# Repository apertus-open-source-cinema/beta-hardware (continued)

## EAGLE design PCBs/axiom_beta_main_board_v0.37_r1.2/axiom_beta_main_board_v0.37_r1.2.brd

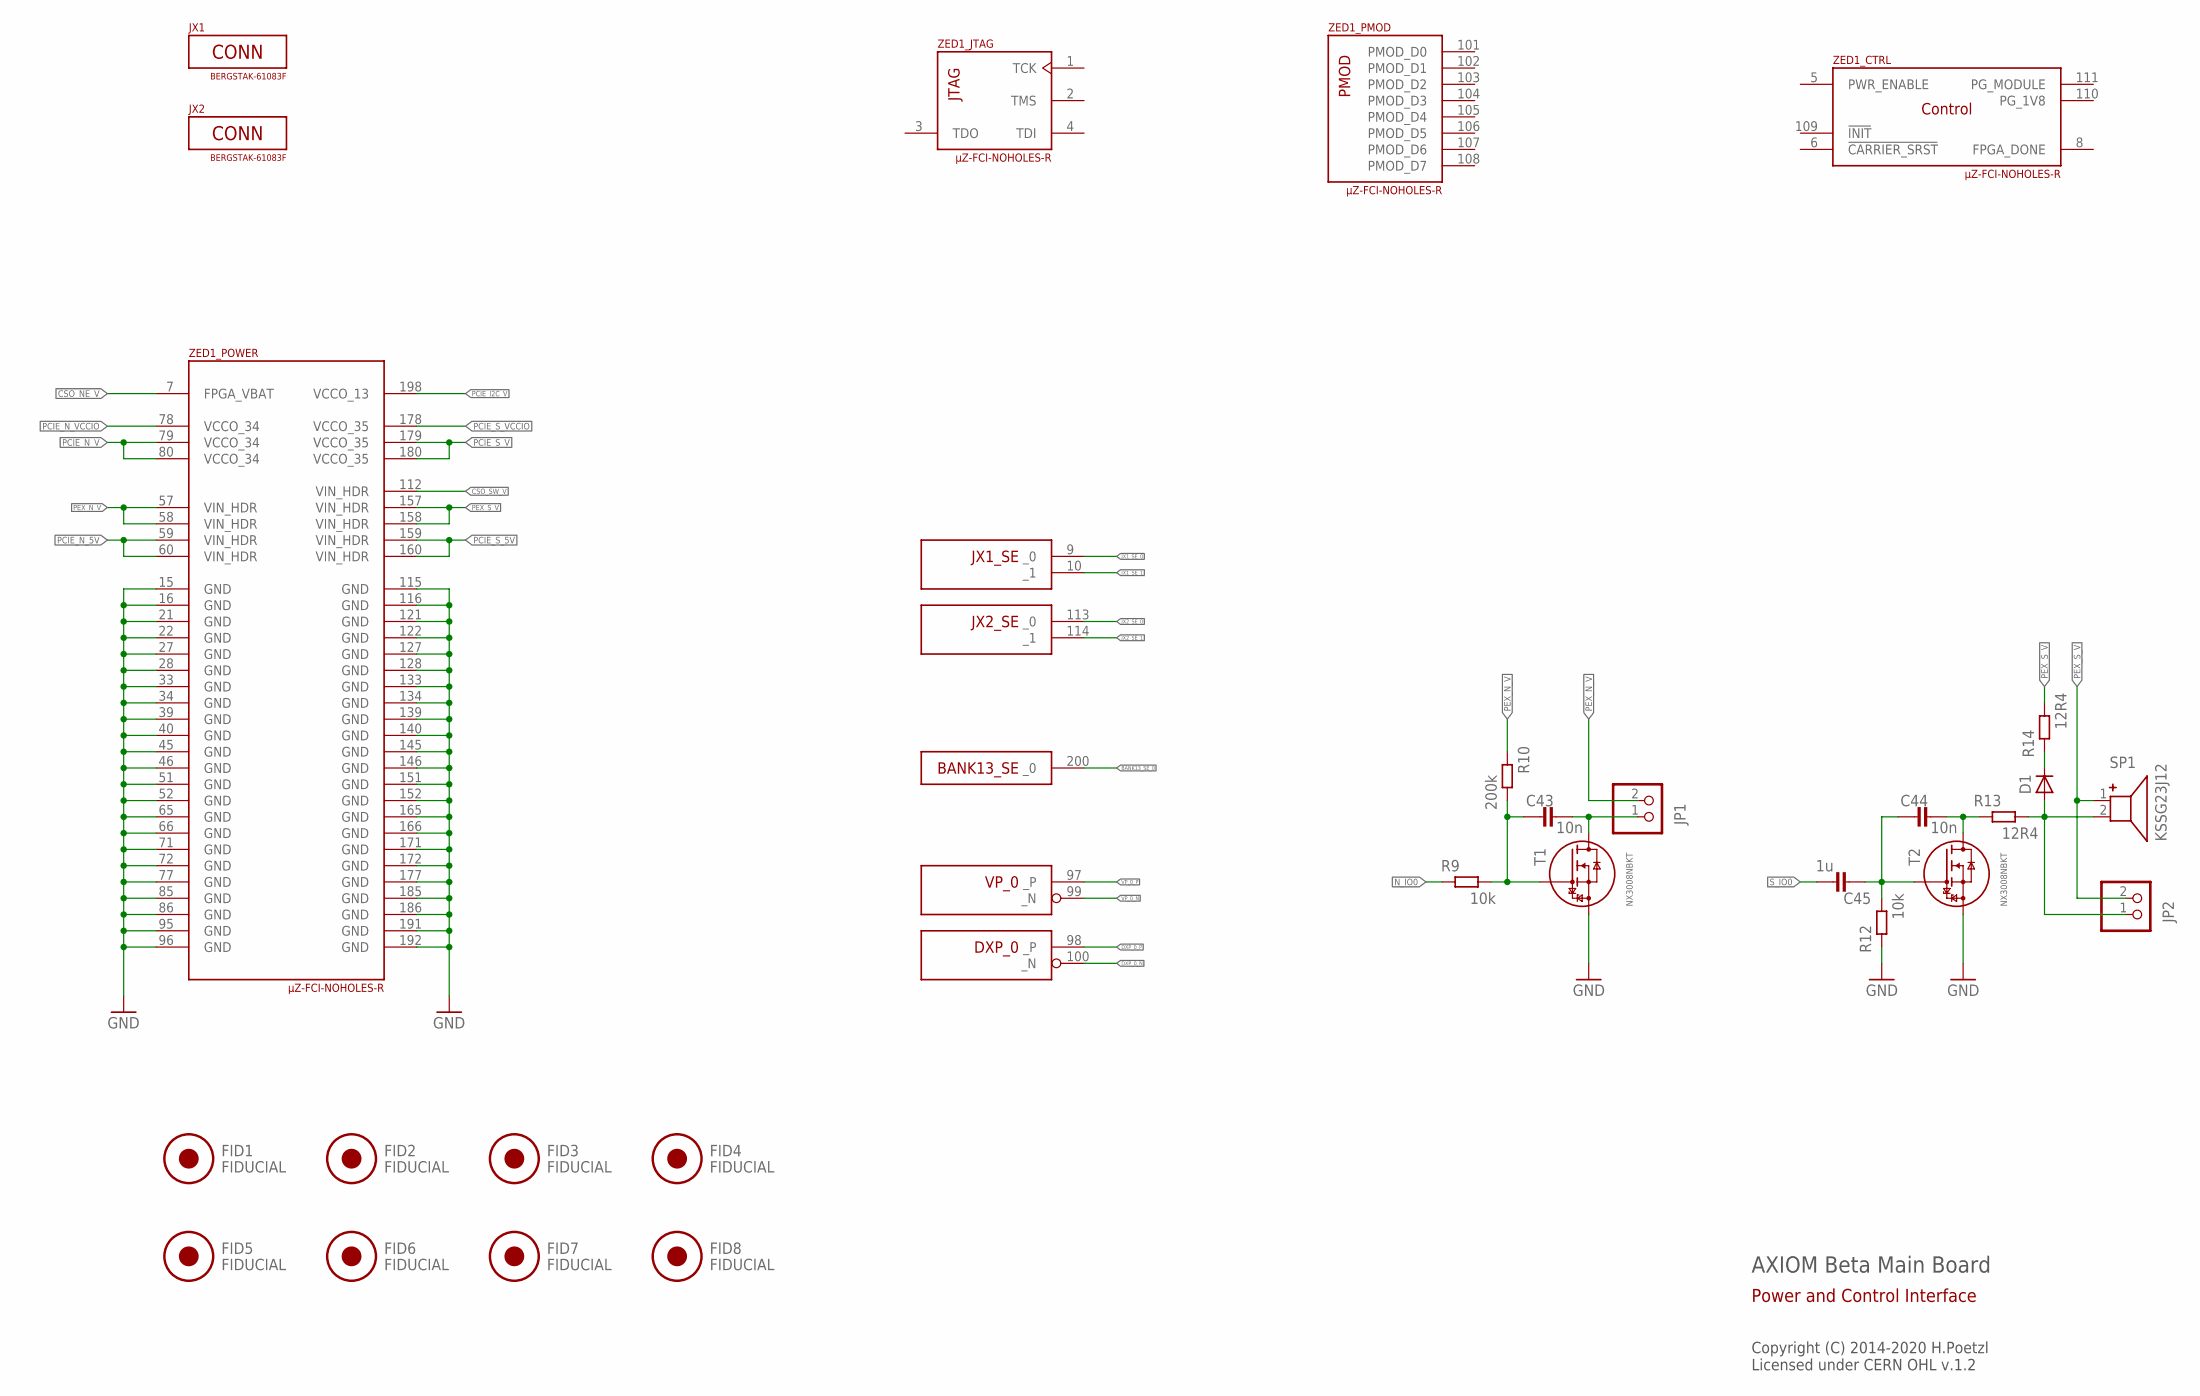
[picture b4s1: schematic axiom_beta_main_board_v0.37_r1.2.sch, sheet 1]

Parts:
C43, C44: 10n; 0402-B
C45: 1u; 0402-B
D1: DB2S20500L; MICROMELF-R; FARNELL 2284949
FID1, FID2, FID3, FID4, FID5, FID6, FID7, FID8: FIDUCIAL; FID_ARROW
JP1: PINHD-1X02_2.00-90°-S; 1X02M/90-S
JP2: PINHD-1X02_2.00; 1X02M
JX1, JX2: BERGSTAK-61083F; 61083-FAKE
R9, R12: 10k; 0402-B
R10: 200k; 0402-B
R13, R14: 12R4; 0402-B
SP1: KSSG23J12
T1, T2: NX3008NBKT; SOT416
ZED1: µZ-FCI-NOHOLES-R; µZ-NOHOLES-R

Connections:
BANK13_SE_0: ZED1.200 (_0); also elsewhere on the board
CSO_NE_V: ZED1.7 (FPGA_VBAT); also elsewhere on the board
CSO_SW_V: ZED1.112 (VIN_HDR); also elsewhere on the board
DXP_0_N: ZED1.100 (_N)
DXP_0_P: ZED1.98 (_P)
GND: R12.1, T1.2 (S), T2.2 (S), ZED1.15 (GND), ZED1.16 (GND), ZED1.21 (GND), ZED1.22 (GND), ZED1.27 (GND), ZED1.28 (GND), ZED1.33 (GND), ZED1.34 (GND), ZED1.39 (GND), ZED1.40 (GND), ZED1.45 (GND), ZED1.46 (GND), ZED1.51 (GND), ZED1.52 (GND), ZED1.65 (GND), ZED1.66 (GND), ZED1.71 (GND), ZED1.72 (GND), ZED1.77 (GND), ZED1.85 (GND), ZED1.86 (GND), ZED1.95 (GND), ZED1.96 (GND), ZED1.115 (GND), ZED1.116 (GND), ZED1.121 (GND), ZED1.122 (GND), ZED1.127 (GND), ZED1.128 (GND), ZED1.133 (GND), ZED1.134 (GND), ZED1.139 (GND), ZED1.140 (GND), ZED1.145 (GND), ZED1.146 (GND), ZED1.151 (GND), ZED1.152 (GND), ZED1.165 (GND), ZED1.166 (GND), ZED1.171 (GND), ZED1.172 (GND), ZED1.177 (GND), ZED1.185 (GND), ZED1.186 (GND), ZED1.191 (GND), ZED1.192 (GND); also elsewhere on the board
JX1_SE_0: ZED1.9 (_0); also elsewhere on the board
JX1_SE_1: ZED1.10 (_1)
JX2_SE_0: ZED1.113 (_0)
JX2_SE_1: ZED1.114 (_1)
unnamed: C43.2, JP1.1, T1.3 (D)
unnamed: C44.2, R13.1, T2.3 (D)
unnamed: D1.C, R14.1
unnamed: D1.A, JP2.1, R13.2, SP1.2
unnamed: C43.1, R9.2, R10.2, T1.1 (G)
unnamed: C44.1, C45.1, R12.2, T2.1 (G)
N_IO0: R9.1; also elsewhere on the board
PCIE_I2C_V: ZED1.198 (VCCO_13); also elsewhere on the board
PCIE_N_5V: ZED1.59 (VIN_HDR), ZED1.60 (VIN_HDR); also elsewhere on the board
PCIE_N_V: ZED1.79 (VCCO_34), ZED1.80 (VCCO_34); also elsewhere on the board
PCIE_N_VCCIO: ZED1.78 (VCCO_34); also elsewhere on the board
PCIE_S_5V: ZED1.159 (VIN_HDR), ZED1.160 (VIN_HDR); also elsewhere on the board
PCIE_S_V: ZED1.179 (VCCO_35), ZED1.180 (VCCO_35); also elsewhere on the board
PCIE_S_VCCIO: ZED1.178 (VCCO_35); also elsewhere on the board
PEX_N_V: JP1.2, R10.1, ZED1.57 (VIN_HDR), ZED1.58 (VIN_HDR)
PEX_S_V: JP2.2, R14.2, SP1.1, ZED1.157 (VIN_HDR), ZED1.158 (VIN_HDR)
S_IO0: C45.2; also elsewhere on the board
VP_0_N: ZED1.99 (_N)
VP_0_P: ZED1.97 (_P)

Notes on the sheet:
AXIOM Beta Main Board
Copyright (C) 2014-2020 H.Poetzl Licensed under CERN OHL v.1.2
Power and Control Interface

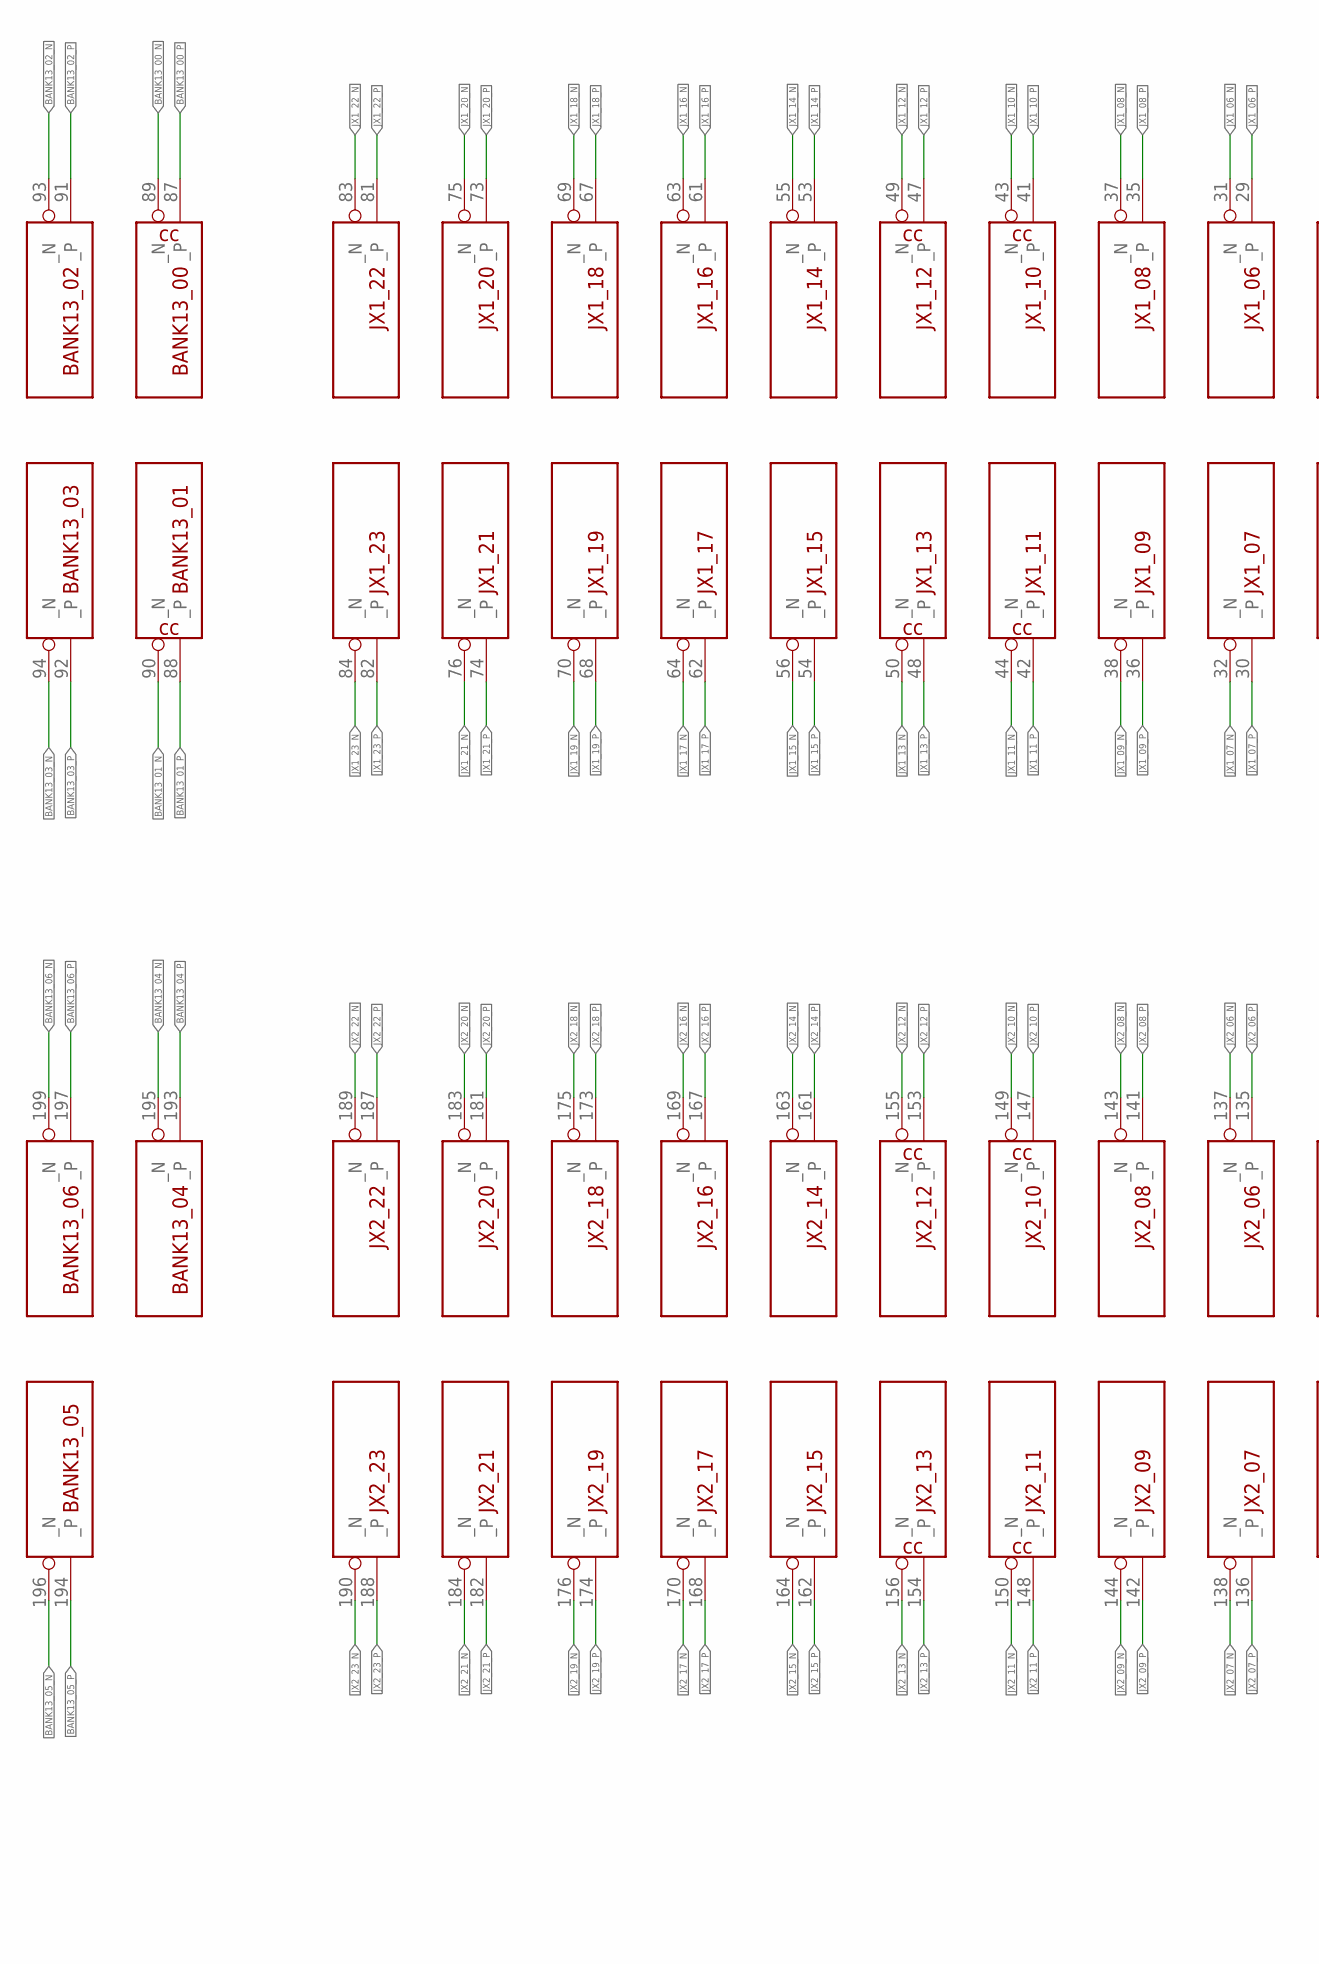
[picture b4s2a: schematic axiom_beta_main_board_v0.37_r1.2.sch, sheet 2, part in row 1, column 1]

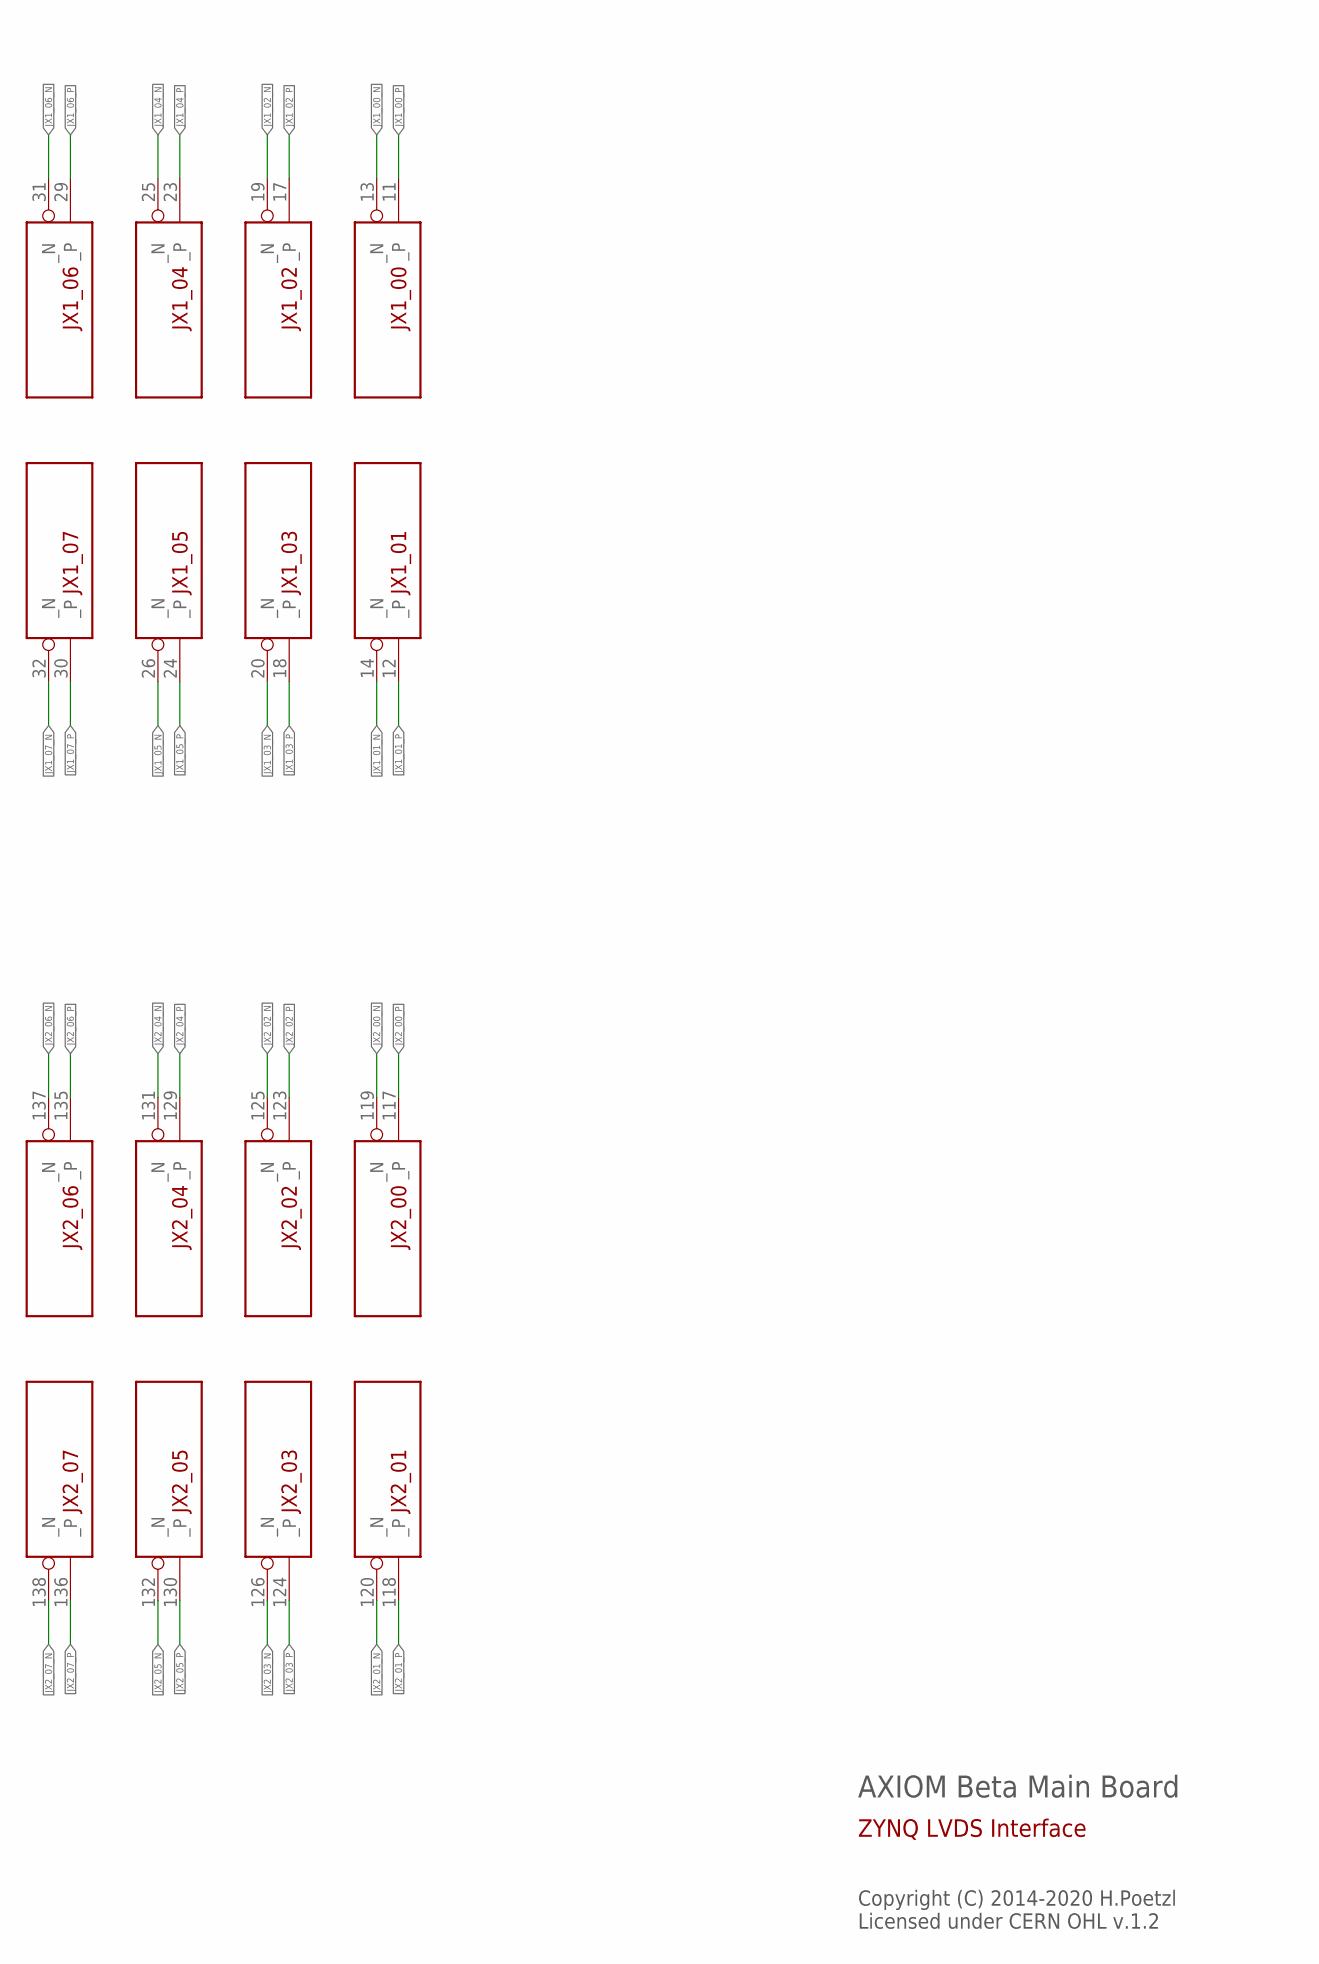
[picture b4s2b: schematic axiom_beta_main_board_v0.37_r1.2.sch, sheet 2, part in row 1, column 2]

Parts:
ZED1: µZ-FCI-NOHOLES-R; µZ-NOHOLES-R

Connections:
BANK13_00_N: ZED1.89 (_N); also elsewhere on the board
BANK13_00_P: ZED1.87 (_P); also elsewhere on the board
BANK13_01_N: ZED1.90 (_N); also elsewhere on the board
BANK13_01_P: ZED1.88 (_P); also elsewhere on the board
BANK13_02_N: ZED1.93 (_N); also elsewhere on the board
BANK13_02_P: ZED1.91 (_P); also elsewhere on the board
BANK13_03_N: ZED1.94 (_N); also elsewhere on the board
BANK13_03_P: ZED1.92 (_P); also elsewhere on the board
BANK13_04_N: ZED1.195 (_N); also elsewhere on the board
BANK13_04_P: ZED1.193 (_P); also elsewhere on the board
BANK13_05_N: ZED1.196 (_N); also elsewhere on the board
BANK13_05_P: ZED1.194 (_P); also elsewhere on the board
BANK13_06_N: ZED1.199 (_N); also elsewhere on the board
BANK13_06_P: ZED1.197 (_P); also elsewhere on the board
JX1_00_N: ZED1.13 (_N); also elsewhere on the board
JX1_00_P: ZED1.11 (_P); also elsewhere on the board
JX1_01_N: ZED1.14 (_N); also elsewhere on the board
JX1_01_P: ZED1.12 (_P); also elsewhere on the board
JX1_02_N: ZED1.19 (_N); also elsewhere on the board
JX1_02_P: ZED1.17 (_P); also elsewhere on the board
JX1_03_N: ZED1.20 (_N); also elsewhere on the board
JX1_03_P: ZED1.18 (_P); also elsewhere on the board
JX1_04_N: ZED1.25 (_N); also elsewhere on the board
JX1_04_P: ZED1.23 (_P); also elsewhere on the board
JX1_05_N: ZED1.26 (_N); also elsewhere on the board
JX1_05_P: ZED1.24 (_P); also elsewhere on the board
JX1_06_N: ZED1.31 (_N); also elsewhere on the board
JX1_06_P: ZED1.29 (_P); also elsewhere on the board
JX1_07_N: ZED1.32 (_N); also elsewhere on the board
JX1_07_P: ZED1.30 (_P); also elsewhere on the board
JX1_08_N: ZED1.37 (_N); also elsewhere on the board
JX1_08_P: ZED1.35 (_P); also elsewhere on the board
JX1_09_N: ZED1.38 (_N); also elsewhere on the board
JX1_09_P: ZED1.36 (_P); also elsewhere on the board
JX1_10_N: ZED1.43 (_N); also elsewhere on the board
JX1_10_P: ZED1.41 (_P); also elsewhere on the board
JX1_11_N: ZED1.44 (_N); also elsewhere on the board
JX1_11_P: ZED1.42 (_P); also elsewhere on the board
JX1_12_N: ZED1.49 (_N); also elsewhere on the board
JX1_12_P: ZED1.47 (_P); also elsewhere on the board
JX1_13_N: ZED1.50 (_N); also elsewhere on the board
JX1_13_P: ZED1.48 (_P); also elsewhere on the board
JX1_14_N: ZED1.55 (_N); also elsewhere on the board
JX1_14_P: ZED1.53 (_P); also elsewhere on the board
JX1_15_N: ZED1.56 (_N); also elsewhere on the board
JX1_15_P: ZED1.54 (_P); also elsewhere on the board
JX1_16_N: ZED1.63 (_N); also elsewhere on the board
JX1_16_P: ZED1.61 (_P); also elsewhere on the board
JX1_17_N: ZED1.64 (_N); also elsewhere on the board
JX1_17_P: ZED1.62 (_P); also elsewhere on the board
JX1_18_N: ZED1.69 (_N); also elsewhere on the board
JX1_18_P: ZED1.67 (_P); also elsewhere on the board
JX1_19_N: ZED1.70 (_N); also elsewhere on the board
JX1_19_P: ZED1.68 (_P); also elsewhere on the board
JX1_20_N: ZED1.75 (_N); also elsewhere on the board
JX1_20_P: ZED1.73 (_P); also elsewhere on the board
JX1_21_N: ZED1.76 (_N); also elsewhere on the board
JX1_21_P: ZED1.74 (_P); also elsewhere on the board
JX1_22_N: ZED1.83 (_N); also elsewhere on the board
JX1_22_P: ZED1.81 (_P); also elsewhere on the board
JX1_23_N: ZED1.84 (_N); also elsewhere on the board
JX1_23_P: ZED1.82 (_P); also elsewhere on the board
JX2_00_N: ZED1.119 (_N); also elsewhere on the board
JX2_00_P: ZED1.117 (_P); also elsewhere on the board
JX2_01_N: ZED1.120 (_N); also elsewhere on the board
JX2_01_P: ZED1.118 (_P); also elsewhere on the board
JX2_02_N: ZED1.125 (_N); also elsewhere on the board
JX2_02_P: ZED1.123 (_P); also elsewhere on the board
JX2_03_N: ZED1.126 (_N); also elsewhere on the board
JX2_03_P: ZED1.124 (_P); also elsewhere on the board
JX2_04_N: ZED1.131 (_N); also elsewhere on the board
JX2_04_P: ZED1.129 (_P); also elsewhere on the board
JX2_05_N: ZED1.132 (_N); also elsewhere on the board
JX2_05_P: ZED1.130 (_P); also elsewhere on the board
JX2_06_N: ZED1.137 (_N); also elsewhere on the board
JX2_06_P: ZED1.135 (_P); also elsewhere on the board
JX2_07_N: ZED1.138 (_N); also elsewhere on the board
JX2_07_P: ZED1.136 (_P); also elsewhere on the board
JX2_08_N: ZED1.143 (_N); also elsewhere on the board
JX2_08_P: ZED1.141 (_P); also elsewhere on the board
JX2_09_N: ZED1.144 (_N); also elsewhere on the board
JX2_09_P: ZED1.142 (_P); also elsewhere on the board
JX2_10_N: ZED1.149 (_N); also elsewhere on the board
JX2_10_P: ZED1.147 (_P); also elsewhere on the board
JX2_11_N: ZED1.150 (_N); also elsewhere on the board
JX2_11_P: ZED1.148 (_P); also elsewhere on the board
JX2_12_N: ZED1.155 (_N); also elsewhere on the board
JX2_12_P: ZED1.153 (_P); also elsewhere on the board
JX2_13_N: ZED1.156 (_N); also elsewhere on the board
JX2_13_P: ZED1.154 (_P); also elsewhere on the board
JX2_14_N: ZED1.163 (_N); also elsewhere on the board
JX2_14_P: ZED1.161 (_P); also elsewhere on the board
JX2_15_N: ZED1.164 (_N); also elsewhere on the board
JX2_15_P: ZED1.162 (_P); also elsewhere on the board
JX2_16_N: ZED1.169 (_N); also elsewhere on the board
JX2_16_P: ZED1.167 (_P); also elsewhere on the board
JX2_17_N: ZED1.170 (_N); also elsewhere on the board
JX2_17_P: ZED1.168 (_P); also elsewhere on the board
JX2_18_N: ZED1.175 (_N); also elsewhere on the board
JX2_18_P: ZED1.173 (_P); also elsewhere on the board
JX2_19_N: ZED1.176 (_N); also elsewhere on the board
JX2_19_P: ZED1.174 (_P); also elsewhere on the board
JX2_20_N: ZED1.183 (_N); also elsewhere on the board
JX2_20_P: ZED1.181 (_P); also elsewhere on the board
JX2_21_N: ZED1.184 (_N); also elsewhere on the board
JX2_21_P: ZED1.182 (_P); also elsewhere on the board
JX2_22_N: ZED1.189 (_N); also elsewhere on the board
JX2_22_P: ZED1.187 (_P); also elsewhere on the board
JX2_23_N: ZED1.190 (_N); also elsewhere on the board
JX2_23_P: ZED1.188 (_P); also elsewhere on the board

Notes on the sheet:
AXIOM Beta Main Board
Copyright (C) 2014-2020 H.Poetzl Licensed under CERN OHL v.1.2
ZYNQ LVDS Interface

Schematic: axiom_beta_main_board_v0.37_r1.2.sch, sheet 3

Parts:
X-EAST: FX10-100/10S; FX10A-100S/10
X-WEST: FX10-100/10S; FX10A-100S/10

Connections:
!E_RESET!: X-EAST.19; also elsewhere on the board
!W_RESET!: X-WEST.19; also elsewhere on the board
E_EN: X-EAST.14; also elsewhere on the board
E_I2C_EN: X-EAST.13; also elsewhere on the board
E_I2C_V: X-EAST.11; also elsewhere on the board
E_SCK: X-EAST.12; also elsewhere on the board
E_SCL: X-EAST.15; also elsewhere on the board
E_SDA: X-EAST.17; also elsewhere on the board
E_SDI: X-EAST.16; also elsewhere on the board
E_SDO: X-EAST.18; also elsewhere on the board
E_SPI_V: X-EAST.21; also elsewhere on the board
E_VE_CV: X-EAST.90; also elsewhere on the board
E_VE_OV: X-EAST.93; also elsewhere on the board
E_VE_UV: X-EAST.91; also elsewhere on the board
GND: X-EAST.5, X-EAST.20, X-EAST.23, X-EAST.26, X-EAST.29, X-EAST.31, X-EAST.32, X-EAST.37, X-EAST.38, X-EAST.43, X-EAST.44, X-EAST.49, X-EAST.50, X-EAST.51, X-EAST.52, X-EAST.57, X-EAST.58, X-EAST.63, X-EAST.64, X-EAST.69, X-EAST.70, X-EAST.71, X-EAST.76, X-EAST.77, X-EAST.82, X-EAST.G1, X-EAST.G2, X-EAST.G3, X-EAST.G4, X-EAST.G5, X-EAST.G6, X-EAST.G7, X-EAST.G8, X-EAST.G9, X-EAST.G10, X-WEST.5, X-WEST.20, X-WEST.23, X-WEST.26, X-WEST.29, X-WEST.31, X-WEST.32, X-WEST.37, X-WEST.38, X-WEST.43, X-WEST.44, X-WEST.49, X-WEST.50, X-WEST.51, X-WEST.52, X-WEST.57, X-WEST.58, X-WEST.63, X-WEST.64, X-WEST.69, X-WEST.70, X-WEST.71, X-WEST.76, X-WEST.77, X-WEST.82, X-WEST.G1, X-WEST.G2, X-WEST.G3, X-WEST.G4, X-WEST.G5, X-WEST.G6, X-WEST.G7, X-WEST.G8, X-WEST.G9, X-WEST.G10; also elsewhere on the board
JTAG_V: X-WEST.21; also elsewhere on the board
JX1_00_N: X-EAST.27; also elsewhere on the board
JX1_00_P: X-EAST.25; also elsewhere on the board
JX1_02_N: X-EAST.24; also elsewhere on the board
JX1_02_P: X-EAST.22; also elsewhere on the board
JX1_04_N: X-EAST.30; also elsewhere on the board
JX1_04_P: X-EAST.28; also elsewhere on the board
JX1_06_N: X-EAST.36; also elsewhere on the board
JX1_06_P: X-EAST.34; also elsewhere on the board
JX1_07_N: X-EAST.35; also elsewhere on the board
JX1_07_P: X-EAST.33; also elsewhere on the board
JX1_08_N: X-EAST.42; also elsewhere on the board
JX1_08_P: X-EAST.40; also elsewhere on the board
JX1_09_N: X-EAST.41; also elsewhere on the board
JX1_09_P: X-EAST.39; also elsewhere on the board
JX1_10_N: X-EAST.48; also elsewhere on the board
JX1_10_P: X-EAST.46; also elsewhere on the board
JX1_11_N: X-EAST.47; also elsewhere on the board
JX1_11_P: X-EAST.45; also elsewhere on the board
JX1_12_N: X-WEST.56; also elsewhere on the board
JX1_12_P: X-WEST.54; also elsewhere on the board
JX1_13_N: X-WEST.55; also elsewhere on the board
JX1_13_P: X-WEST.53; also elsewhere on the board
JX1_14_N: X-WEST.62; also elsewhere on the board
JX1_14_P: X-WEST.60; also elsewhere on the board
JX1_15_N: X-WEST.61; also elsewhere on the board
JX1_15_P: X-WEST.59; also elsewhere on the board
JX1_16_N: X-WEST.68; also elsewhere on the board
JX1_16_P: X-WEST.66; also elsewhere on the board
JX1_17_N: X-WEST.67; also elsewhere on the board
JX1_17_P: X-WEST.65; also elsewhere on the board
JX1_18_N: X-WEST.74; also elsewhere on the board
JX1_18_P: X-WEST.72; also elsewhere on the board
JX1_20_N: X-WEST.80; also elsewhere on the board
JX1_20_P: X-WEST.78; also elsewhere on the board
JX1_22_N: X-WEST.75; also elsewhere on the board
JX1_22_P: X-WEST.73; also elsewhere on the board
JX2_01_N: X-EAST.73; also elsewhere on the board
JX2_01_P: X-EAST.75; also elsewhere on the board
JX2_03_N: X-EAST.78; also elsewhere on the board
JX2_03_P: X-EAST.80; also elsewhere on the board
JX2_05_N: X-EAST.72; also elsewhere on the board
JX2_05_P: X-EAST.74; also elsewhere on the board
JX2_06_N: X-EAST.65; also elsewhere on the board
JX2_06_P: X-EAST.67; also elsewhere on the board
JX2_07_N: X-EAST.66; also elsewhere on the board
JX2_07_P: X-EAST.68; also elsewhere on the board
JX2_08_N: X-EAST.59; also elsewhere on the board
JX2_08_P: X-EAST.61; also elsewhere on the board
JX2_09_N: X-EAST.60; also elsewhere on the board
JX2_09_P: X-EAST.62; also elsewhere on the board
JX2_10_N: X-EAST.53; also elsewhere on the board
JX2_10_P: X-EAST.55; also elsewhere on the board
JX2_11_N: X-EAST.54; also elsewhere on the board
JX2_11_P: X-EAST.56; also elsewhere on the board
JX2_12_N: X-WEST.45; also elsewhere on the board
JX2_12_P: X-WEST.47; also elsewhere on the board
JX2_13_N: X-WEST.46; also elsewhere on the board
JX2_13_P: X-WEST.48; also elsewhere on the board
JX2_14_N: X-WEST.39; also elsewhere on the board
JX2_14_P: X-WEST.41; also elsewhere on the board
JX2_15_N: X-WEST.40; also elsewhere on the board
JX2_15_P: X-WEST.42; also elsewhere on the board
JX2_16_N: X-WEST.33; also elsewhere on the board
JX2_16_P: X-WEST.35; also elsewhere on the board
JX2_17_N: X-WEST.34; also elsewhere on the board
JX2_17_P: X-WEST.36; also elsewhere on the board
JX2_19_N: X-WEST.28; also elsewhere on the board
JX2_19_P: X-WEST.30; also elsewhere on the board
JX2_21_N: X-WEST.22; also elsewhere on the board
JX2_21_P: X-WEST.24; also elsewhere on the board
JX2_23_N: X-WEST.25; also elsewhere on the board
JX2_23_P: X-WEST.27; also elsewhere on the board
N_CHK_EN: X-WEST.94
N_CHK_V: X-WEST.92; also elsewhere on the board
N_I2C_EN: X-EAST.7; also elsewhere on the board
N_I2C_V: X-EAST.9; also elsewhere on the board
N_SCK: X-EAST.2; also elsewhere on the board
N_SCL: X-EAST.1; also elsewhere on the board
N_SDA: X-EAST.3; also elsewhere on the board
N_SDI: X-EAST.6; also elsewhere on the board
N_SDO: X-EAST.4; also elsewhere on the board
N_SPI_EN: X-EAST.8; also elsewhere on the board
N_SPI_V: X-EAST.10; also elsewhere on the board
N_VE_CV: X-WEST.96; also elsewhere on the board
N_VE_OV: X-WEST.95; also elsewhere on the board
N_VE_RS: X-WEST.88; also elsewhere on the board
N_VE_UV: X-WEST.85; also elsewhere on the board
N_VN_CV: X-WEST.98; also elsewhere on the board
N_VN_OV: X-WEST.97; also elsewhere on the board
N_VN_RS: X-WEST.86; also elsewhere on the board
N_VN_UV: X-WEST.87; also elsewhere on the board
N_VW_CV: X-WEST.100; also elsewhere on the board
N_VW_OV: X-WEST.99; also elsewhere on the board
N_VW_RS: X-WEST.84; also elsewhere on the board
N_VW_UV: X-WEST.89; also elsewhere on the board
RES1: X-WEST.79
RES2: X-WEST.81
RES3: X-WEST.83
RES4: X-EAST.79
RES5: X-EAST.81
RES6: X-EAST.83
S_CHK_EN: X-EAST.94
S_CHK_V: X-EAST.92; also elsewhere on the board
S_I2C_EN: X-WEST.7; also elsewhere on the board
S_I2C_V: X-WEST.9; also elsewhere on the board
S_SCK: X-WEST.2; also elsewhere on the board
S_SCL: X-WEST.1; also elsewhere on the board
S_SDA: X-WEST.3; also elsewhere on the board
S_SDI: X-WEST.6; also elsewhere on the board
S_SDO: X-WEST.4; also elsewhere on the board
S_SPI_EN: X-WEST.8; also elsewhere on the board
S_SPI_V: X-WEST.10; also elsewhere on the board
S_VE_CV: X-EAST.100; also elsewhere on the board
S_VE_OV: X-EAST.99; also elsewhere on the board
S_VE_RS: X-EAST.84; also elsewhere on the board
S_VE_UV: X-EAST.89; also elsewhere on the board
S_VS_CV: X-EAST.98; also elsewhere on the board
S_VS_OV: X-EAST.97; also elsewhere on the board
S_VS_RS: X-EAST.86; also elsewhere on the board
S_VS_UV: X-EAST.87; also elsewhere on the board
S_VW_CV: X-EAST.96; also elsewhere on the board
S_VW_OV: X-EAST.95; also elsewhere on the board
S_VW_RS: X-EAST.88; also elsewhere on the board
S_VW_UV: X-EAST.85; also elsewhere on the board
TCK: X-WEST.12; also elsewhere on the board
TDI: X-WEST.16; also elsewhere on the board
TDO: X-WEST.18; also elsewhere on the board
TMS: X-WEST.14; also elsewhere on the board
W_I2C_EN: X-WEST.13; also elsewhere on the board
W_I2C_V: X-WEST.11; also elsewhere on the board
W_SCL: X-WEST.15; also elsewhere on the board
W_SDA: X-WEST.17; also elsewhere on the board
W_VW_CV: X-WEST.90; also elsewhere on the board
W_VW_OV: X-WEST.93; also elsewhere on the board
W_VW_UV: X-WEST.91; also elsewhere on the board

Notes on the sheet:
AXIOM Beta Main Board
Copyright (C) 2014-2020 H.Poetzl Licensed under CERN OHL v.1.2
Interface Board Connection
